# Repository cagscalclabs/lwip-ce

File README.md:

# lwIP-CE

**lwIP** is a small networking stack built for low-resource embedded systems, maintained by [nonGNU](https://github.com/lwip-tcpip/lwip). **lwIP-CE** is a fork of it targeting the Texas Instruments TI-84+ CE graphing calculator, shipped as a dynamic library (libload) with a TLS 1.3 client stack, a USB CDC-ECM/NCM Ethernet driver, Wi-Fi through an ESP32-S3 or ESP32-P4 bridge (firmware in [`wifi_bridge/`](./wifi_bridge)), and an app-facing socket API. The original upstream readme is [here](./README-ORIG.md).

**Truststore Latest (required for TLS connections):** **https://github.com/cagscalclabs/lwip-ce/releases/tag/truststore-latest**

**Full documentation, API reference, and getting-started guide:** **https://cagscalclabs.github.io/lwip-ce/index.html**

**Whitepaper** (architecture, threat model, validation methodology): **https://github.com/cagscalclabs/lwip-ce/releases/tag/whitepaper-latest**
*It's long so prepare yourself. But I wanted a descriptive, forward facing document for technical auditing.*

## Quick orientation

- Programs link against lwIP-CE as a libload dynamic library, not by compiling `src/` in. See [Getting Started](https://cagscalclabs.github.io/lwip-ce/getting-started.html) for installation and the required init sequence (`lwip_start()` → `lwip_network_up()` → socket API).
- The app-facing API is `lwip_socket_*` (create/connect/read/write/close) — a small, fixed verb set over TCP/UDP/TLS. Lower-level lwIP primitives (raw `tcp_*`/`udp_*` PCB callbacks) are still available for advanced use; see `lwip.h` and the doc site for both layers.
- TLS, the custom allocator, the USB Ethernet driver, and the truststore/CI validation pipeline are all covered in depth in the whitepaper and the doc site — this README intentionally stays short.

## TLS 1.3 overview

- **Cipher suites:** TLS_AES_128_GCM_SHA256 (`0x1301`), TLS_AES_256_GCM_SHA384 (`0x1302`), TLS_AES_128_CCM_SHA256 (`0x1304`). PSK/resumption offers only the SHA-256 suites (binder hash binding).
- **Key exchange:** X25519 (preferred) and secp256r1/P-256 via HelloRetryRequest. The P-384 ECDHE primitives exist, but the secp384r1 group (`0x0018`) is not offered.
- **Signatures:** RSA-PKCS#1 v1.5 and RSA-PSS-SHA256, ECDSA P-256/SHA-256, and ECDSA P-384/SHA-384 (`ecdsa_secp384r1_sha384`, `0x0503`, offered last / least preferred).
- **Hashes:** SHA-256, SHA-384, and SHA-512 are implemented and available through the hash, HMAC, HKDF, PBKDF2, and MGF1 APIs. TLS 1.3 negotiates SHA-256 or SHA-384 per cipher suite; no RFC 8446 suite uses SHA-512.
- **Truststore roots:** RSA, EC P-256, and EC P-384 anchors are accepted (P-384 added as `alg_id` 3); chain links verify RSA/SHA-256, ECDSA P-256/SHA-256, and ECDSA P-384/SHA-384.
- **Keys API:** `tls_key_import` accepts RSA, P-256, and P-384 keys; `tls_key_sign`/`tls_key_verify` support ECDSA P-256/P-384 (RFC 6979, raw `r||s` or DER). RSA private signing is not implemented.

## Related media

- First Beta Test: https://www.youtube.com/watch?v=fD2n7CzFeZU
- TCP and TLS Chat test: https://youtu.be/rX79owIVM-o
- Curated DAST test suite: https://www.youtube.com/shorts/APBYBo0O6sg
- IRC demo: https://www.youtube.com/watch?v=40q8J8R70nE

## Contributors

Special thanks to:

- commandblockguy (initial lwIP porting)
- beckadamtheinventor (SHA-256 assembly rewrite)
- jacobly (RSA-2048)
- _PT (X25519 ECDHE)
- calc84maniac (AES optimization, assembly rewrite)
- alessiodam (WiFi drivers and hardware - custom PCB and firmware)
- TIny_Hacker (fasmg to GAS conversion help)
- Zeroko (entropy analysis)
- acagliano (CDC Ethernet driver, memory subsystem, TLS implementation, RFC compliance)

And thanks to Adriweb for making weird sporadic CEmu feature additions to help me debug this insanity without wanting to fling myself (or my computer or calculator) out my window (though I can't confirm that didn't almost happen anyway).

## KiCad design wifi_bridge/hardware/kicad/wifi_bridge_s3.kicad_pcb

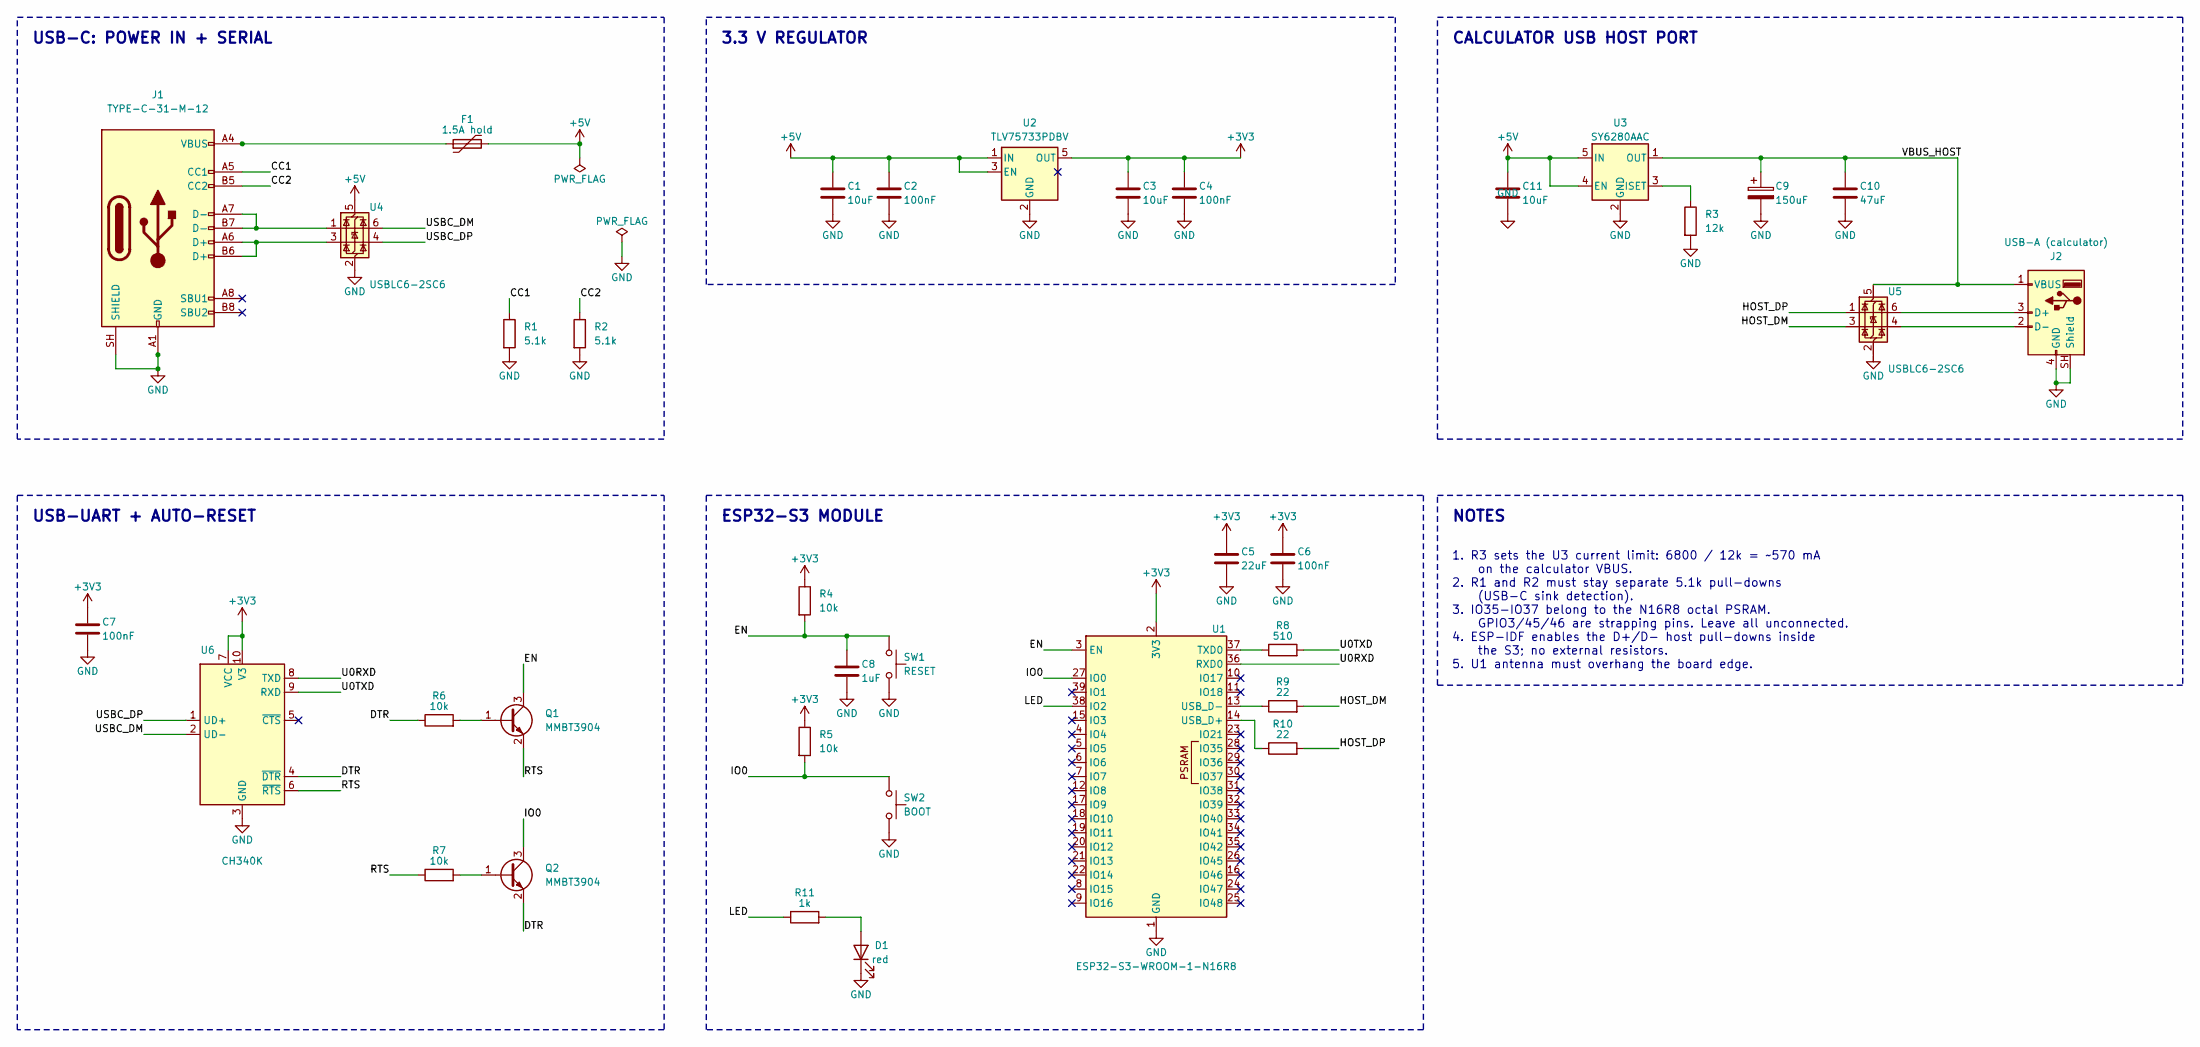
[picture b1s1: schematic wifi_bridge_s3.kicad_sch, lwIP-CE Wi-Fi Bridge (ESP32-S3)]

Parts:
C1, C3, C11: 10uF; C_0603_1608Metric; LCSC C19702
C2, C4, C6, C7: 100nF; C_0402_1005Metric; LCSC C1525
C5: 22uF; C_0805_2012Metric; LCSC C45783
C8: 1uF; C_0402_1005Metric; LCSC C52923
C9: 150uF; CP_EIA-6032-28_Kemet-C; LCSC C600588
C10: 47uF; C_1206_3216Metric; LCSC C96123
D1: red; LED_0603_1608Metric; LCSC C2286
F1: 1.5A hold; Fuse_1206_3216Metric; LCSC C2937115
J1: TYPE-C-31-M-12; USB_C_Receptacle_HRO_TYPE-C-31-M-12; LCSC C165948
J2: USB-A (calculator); USB-A-TH_10.0QHHTZB6.3; LCSC C668591
Q1, Q2: MMBT3904; SOT-23; LCSC C20526
R1, R2: 5.1k; R_0402_1005Metric; LCSC C25905
R3: 12k; R_0402_1005Metric; LCSC C25752
R4, R5, R6, R7: 10k; R_0402_1005Metric; LCSC C25744
R8: 510; R_0402_1005Metric; LCSC C25123
R9, R10: 22; R_0402_1005Metric; LCSC C25092
R11: 1k; R_0402_1005Metric; LCSC C11702
SW1: RESET; SW-SMD_L3.9-W3.0-P4.45; LCSC C720477
SW2: BOOT; SW-SMD_L3.9-W3.0-P4.45; LCSC C720477
U1: ESP32-S3-WROOM-1-N16R8; ESP32-S3-WROOM-1; LCSC C2913202
U2: TLV75733PDBV; SOT-23-5; LCSC C485517
U3: SY6280AAC; SOT-23-5_L3.0-W1.7-P0.95-LS2.8-BL; LCSC C55136
U4, U5: USBLC6-2SC6; SOT-23-6; LCSC C2687116
U6: CH340K; SSOP-10-1EP_3.9x4.9mm_P1mm_EP2.1x3.3mm; LCSC C18208922

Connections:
+3V3: C3.1, C4.1, C5.1, C6.1, C7.1, R4.1, R5.1, U1.2 (3V3), U2.5 (OUT), U6.7 (VCC), U6.10 (V3)
+5V: C1.1, C2.1, C11.1, F1.2, U2.1 (IN), U2.3 (EN), U3.4 (EN), U3.5 (IN), U4.5 (VBUS)
/CC1: J1.A5 (CC1), R1.1
/CC2: J1.B5 (CC2), R2.1
/DTR: Q2.2 (E), R6.1, U6.4 (~DTR)
/EN: C8.1, Q1.3 (C), R4.2, SW1.1, U1.3 (EN)
/HOST_DM: R9.2, U5.3 (I/O2)
/HOST_DP: R10.2, U5.1 (I/O1)
/IO0: Q2.3 (C), R5.2, SW2.1, U1.27 (IO0)
/LED: R11.1, U1.38 (IO2)
/RTS: Q1.2 (E), R7.1, U6.6 (~RTS)
/U0RXD: U1.36 (RXD0), U6.8 (TXD)
/U0TXD: R8.2, U6.9 (RXD)
/USBC_DM: U4.6 (I/O1), U6.2 (UD-)
/USBC_DP: U4.4 (I/O2), U6.1 (UD+)
/VBUS_HOST: C9.1, C10.1, J2.1 (VBUS), U3.1 (OUT), U5.5 (VBUS)
GND: C1.2, C2.2, C3.2, C4.2, C5.2, C6.2, C7.2, C8.2, C9.2, C10.2, C11.2, D1.1 (K), J1.A1 (GND), J1.A12 (GND), J1.B1 (GND), J1.B12 (GND), J1.SH (SHIELD), J2.4 (GND), J2.SH (Shield), R1.2, R2.2, R3.2, SW1.2, SW2.2, U1.1 (GND), U1.40 (GND), U1.41 (GND), U2.2 (GND), U3.2 (GND), U4.2 (GND), U5.2 (GND), U6.3 (GND), U6.11 (GND)
unnamed: D1.2 (A), R11.2
unnamed: F1.1, J1.A4 (VBUS), J1.A9 (VBUS), J1.B4 (VBUS), J1.B9 (VBUS)
unnamed: J1.A6 (D+), J1.B6 (D+), U4.3 (I/O2)
unnamed: J1.A7 (D-), J1.B7 (D-), U4.1 (I/O1)
unnamed: J2.3 (D+), U5.6 (I/O1)
unnamed: J2.2 (D-), U5.4 (I/O2)
unnamed: Q1.1 (B), R6.2
unnamed: Q2.1 (B), R7.2
unnamed: R8.1, U1.37 (TXD0)
unnamed: R10.1, U1.14 (USB_D+)
unnamed: R9.1, U1.13 (USB_D-)
unnamed: R3.1, U3.3 (ISET)

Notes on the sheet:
1. R3 sets the U3 current limit: 6800 / 12k = ~570 mA on the calculator VBUS. 2. R1 and R2 must stay separate 5.1k pull-downs (USB-C sink detection). 3. IO35-IO37 belong to the N16R8 octal PSRAM. GPIO3/45/46 are strapping pins. Leave all unconnected. 4. ESP-IDF enables the D+/D- host pull-downs ins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
NOTES
ESP32-S3 MODULE
CALCULATOR USB HOST PORT
USB-C: POWER IN + SERIAL
3.3 V REGULATOR
USB-UART + AUTO-RESET

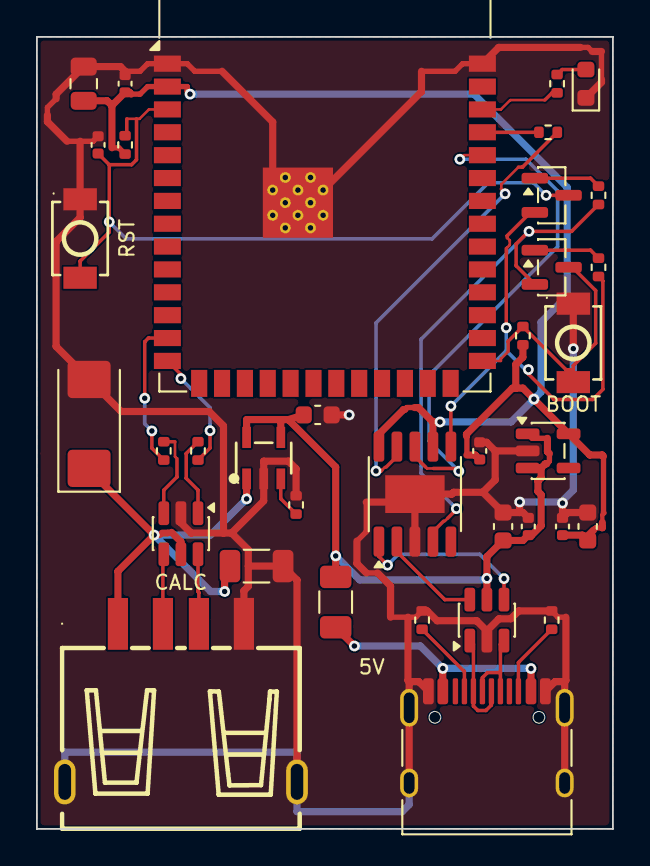
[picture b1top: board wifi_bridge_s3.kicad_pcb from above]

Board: 2 copper layers, 32.0 x 44.0 mm, 36 parts (0 on the bottom side), 29 nets.

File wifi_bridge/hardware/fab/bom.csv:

"Comment","Designator","Footprint","LCSC","Quantity"
"10uF","C1,C3,C11","Capacitor_SMD:C_0603_1608Metric","C19702","3"
"100nF","C2,C4,C6,C7","Capacitor_SMD:C_0402_1005Metric","C1525","4"
"22uF","C5","Capacitor_SMD:C_0805_2012Metric","C45783","1"
"1uF","C8","Capacitor_SMD:C_0402_1005Metric","C52923","1"
"150uF","C9","Capacitor_Tantalum_SMD:CP_EIA-6032-28_Kemet-C","C600588","1"
"47uF","C10","Capacitor_SMD:C_1206_3216Metric","C96123","1"
"red","D1","LED_SMD:LED_0603_1608Metric","C2286","1"
"1.5A hold","F1","Fuse:Fuse_1206_3216Metric","C2937115","1"
"TYPE-C-31-M-12","J1","lcsc:USB_C_Receptacle_HRO_TYPE-C-31-M-12","C165948","1"
"USB-A (calculator)","J2","lcsc:USB-A-TH_10.0QHHTZB6.3","C668591","1"
"MMBT3904","Q1,Q2","Package_TO_SOT_SMD:SOT-23","C20526","2"
"5.1k","R1,R2","Resistor_SMD:R_0402_1005Metric","C25905","2"
"12k","R3","Resistor_SMD:R_0402_1005Metric","C25752","1"
"10k","R4,R5,R6,R7","Resistor_SMD:R_0402_1005Metric","C25744","4"
"510","R8","Resistor_SMD:R_0402_1005Metric","C25123","1"
"22","R9,R10","Resistor_SMD:R_0402_1005Metric","C25092","2"
"1k","R11","Resistor_SMD:R_0402_1005Metric","C11702","1"
"RESET / BOOT","SW1,SW2","lcsc:SW-SMD_L3.9-W3.0-P4.45","C720477","2"
"ESP32-S3-WROOM-1-N16R8","U1","RF_Module:ESP32-S3-WROOM-1","C2913202","1"
"TLV75733PDBV","U2","Package_TO_SOT_SMD:SOT-23-5","C485517","1"
"SY6280AAC","U3","lcsc:SOT-23-5_L3.0-W1.7-P0.95-LS2.8-BL","C55136","1"
"USBLC6-2SC6","U4,U5","Package_TO_SOT_SMD:SOT-23-6","C2687116","2"
"CH340K","U6","Package_SO:SSOP-10-1EP_3.9x4.9mm_P1mm_EP2.1x3.3mm","C18208922","1"
